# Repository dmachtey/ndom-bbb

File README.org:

* High density BBB domotic cape.
  - 32 opto inputs +32 opto outputs for BeagleBone Black
  - this board is intended to be used for domotics or whatever you
    want.
  - It has Push-in spring's connectors for easiness and space reduction
  - All inputs and outputs are gated though =GPIO3_15=
  - There are two more boards on this project:
    - "relay-board" is a single relay board.
    - "out-board" is a high current (10A) Mosfet Board intended for
      (soft) PWM LEDs, up to 60 volts

#+ATTR_LaTeX: :width 10cm\textwidth :options angle=0 :placement [H]
[[https://github.com/dmachtey/ndom-bbb/blob/master/images/domcape8.jpg]]

* Contact information
  - Damian Machtey
  - dmachtey at gmail com
* License
  - Hardware is released under [[http://creativecommons.org/licenses/by-sa/4.0/][Creative Commons Sharealike 4.0
    International]]
    [[file:https://i.creativecommons.org/l/by-sa/4.0/88x31.png]]
  - Software is released under GNU General Public License
    http://www.gnu.org/licenses/
  - © 2017 Damian Machtey

* Fell free to use this project
  - Just please let me know
  - and if you manufacture the board please keep my name on it.

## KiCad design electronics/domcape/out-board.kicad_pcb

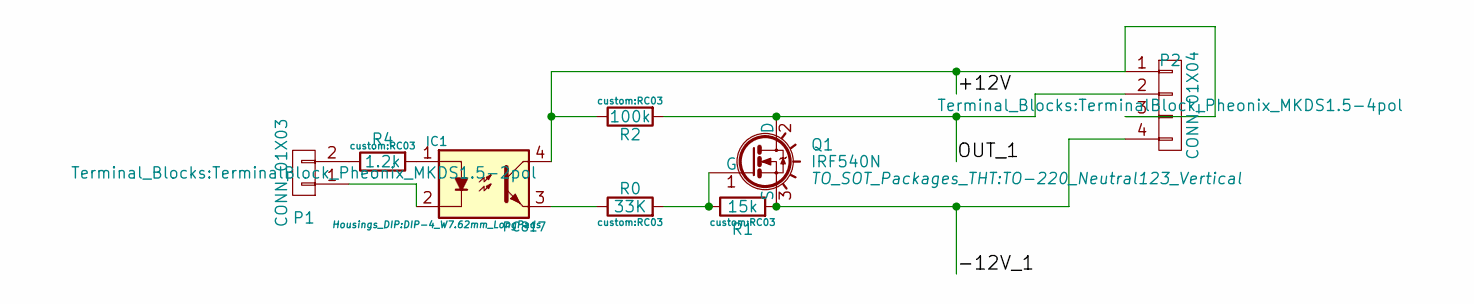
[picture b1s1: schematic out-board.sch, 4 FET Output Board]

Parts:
IC1: PC817; DIP-4_W7.62mm_LongPads
P1: CONN_01X03; TerminalBlock_Pheonix_MKDS1.5-2pol
P2: CONN_01X04; TerminalBlock_Pheonix_MKDS1.5-4pol
Q1: IRF540N; TO-220_Neutral123_Vertical
R0: 33K; RC03
R1: 15k; RC03
R2: 100k; RC03
R4: 1.2k; RC03

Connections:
/+12V: IC1.4, P2.1, P2.3, R2.1
/-12V_1: P2.4, Q1.3 (S), R1.2
/OUT_1: P2.2, Q1.2 (D), R2.2
unnamed: IC1.1, R4.2
unnamed: IC1.2, P1.1
unnamed: IC1.3, R0.1
unnamed: P1.2, R4.1
unnamed: Q1.1 (G), R0.2, R1.1

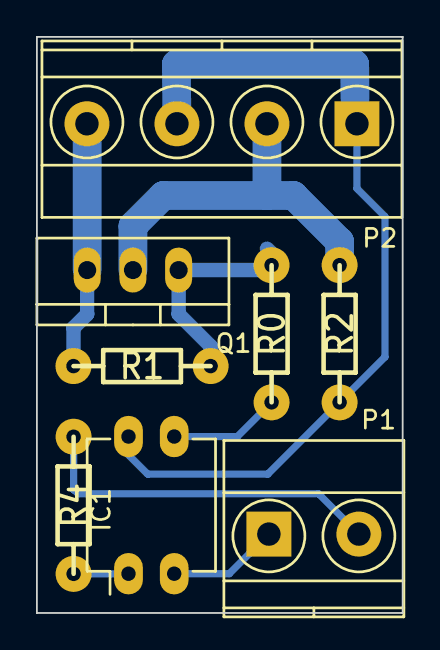
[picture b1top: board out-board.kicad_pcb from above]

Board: 2 copper layers, 20.3 x 32.0 mm, 8 parts (0 on the bottom side), 8 nets.

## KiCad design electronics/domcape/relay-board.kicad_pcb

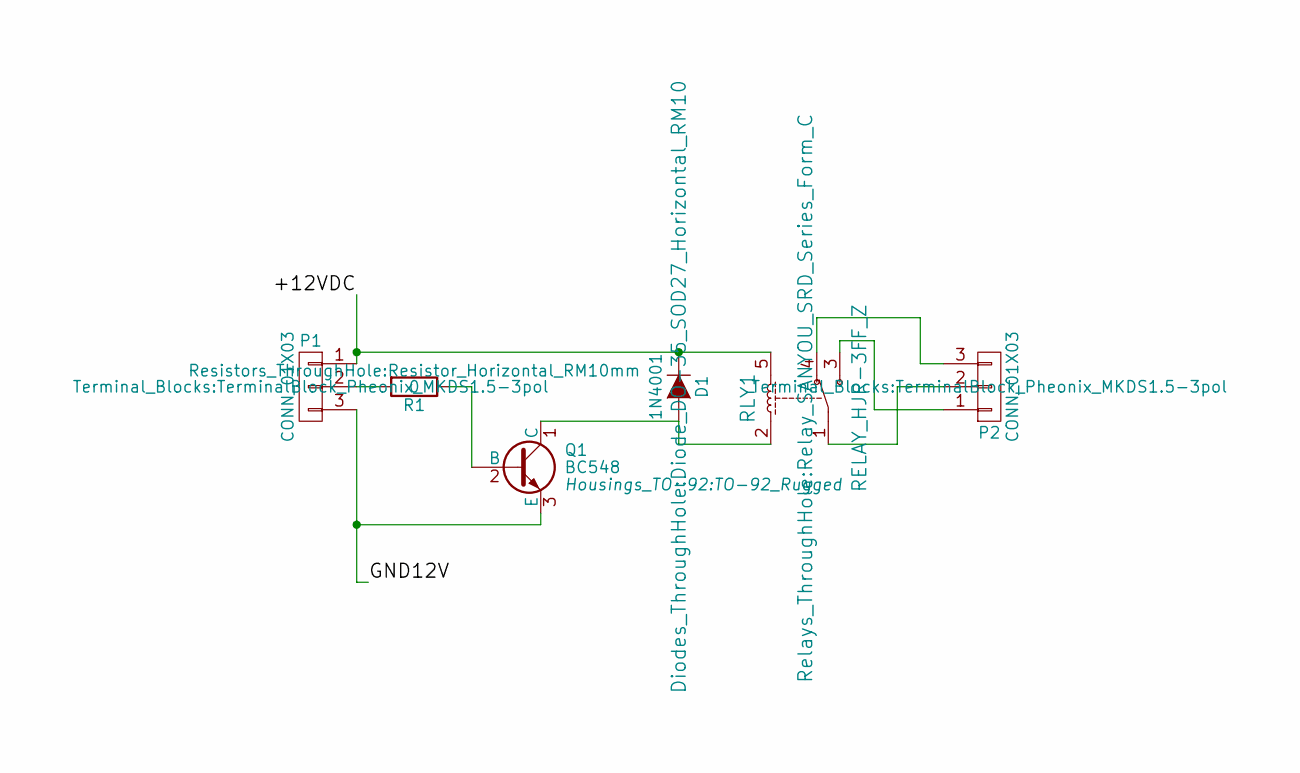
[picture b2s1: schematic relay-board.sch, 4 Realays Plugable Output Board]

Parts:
D1: 1N4001; Diode_DO-35_SOD27_Horizontal_RM10
P1, P2: CONN_01X03; TerminalBlock_Pheonix_MKDS1.5-3pol
Q1: BC548; TO-92_Rugged
R1: 0; Resistor_Horizontal_RM10mm
RLY1: RELAY_HJR-3FF_Z; Relay_SANYOU_SRD_Series_Form_C

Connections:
/+12VDC: D1.1 (K), P1.1, RLY1.5
/GND12V: P1.3, Q1.3 (E)
unnamed: D1.2 (A), Q1.1 (C), RLY1.2
unnamed: P1.2, R1.2
unnamed: P2.1, RLY1.3
unnamed: P2.2, RLY1.1
unnamed: P2.3, RLY1.4
unnamed: Q1.2 (B), R1.1

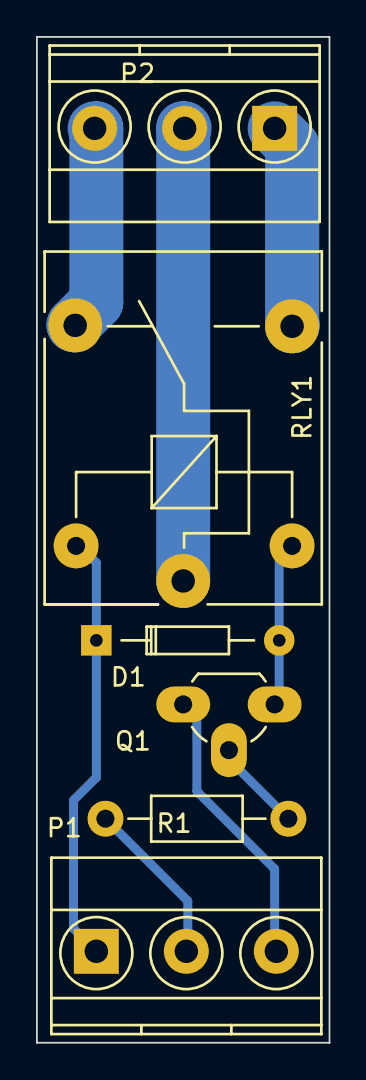
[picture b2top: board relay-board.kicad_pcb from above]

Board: 2 copper layers, 16.3 x 55.9 mm, 6 parts (0 on the bottom side), 8 nets.

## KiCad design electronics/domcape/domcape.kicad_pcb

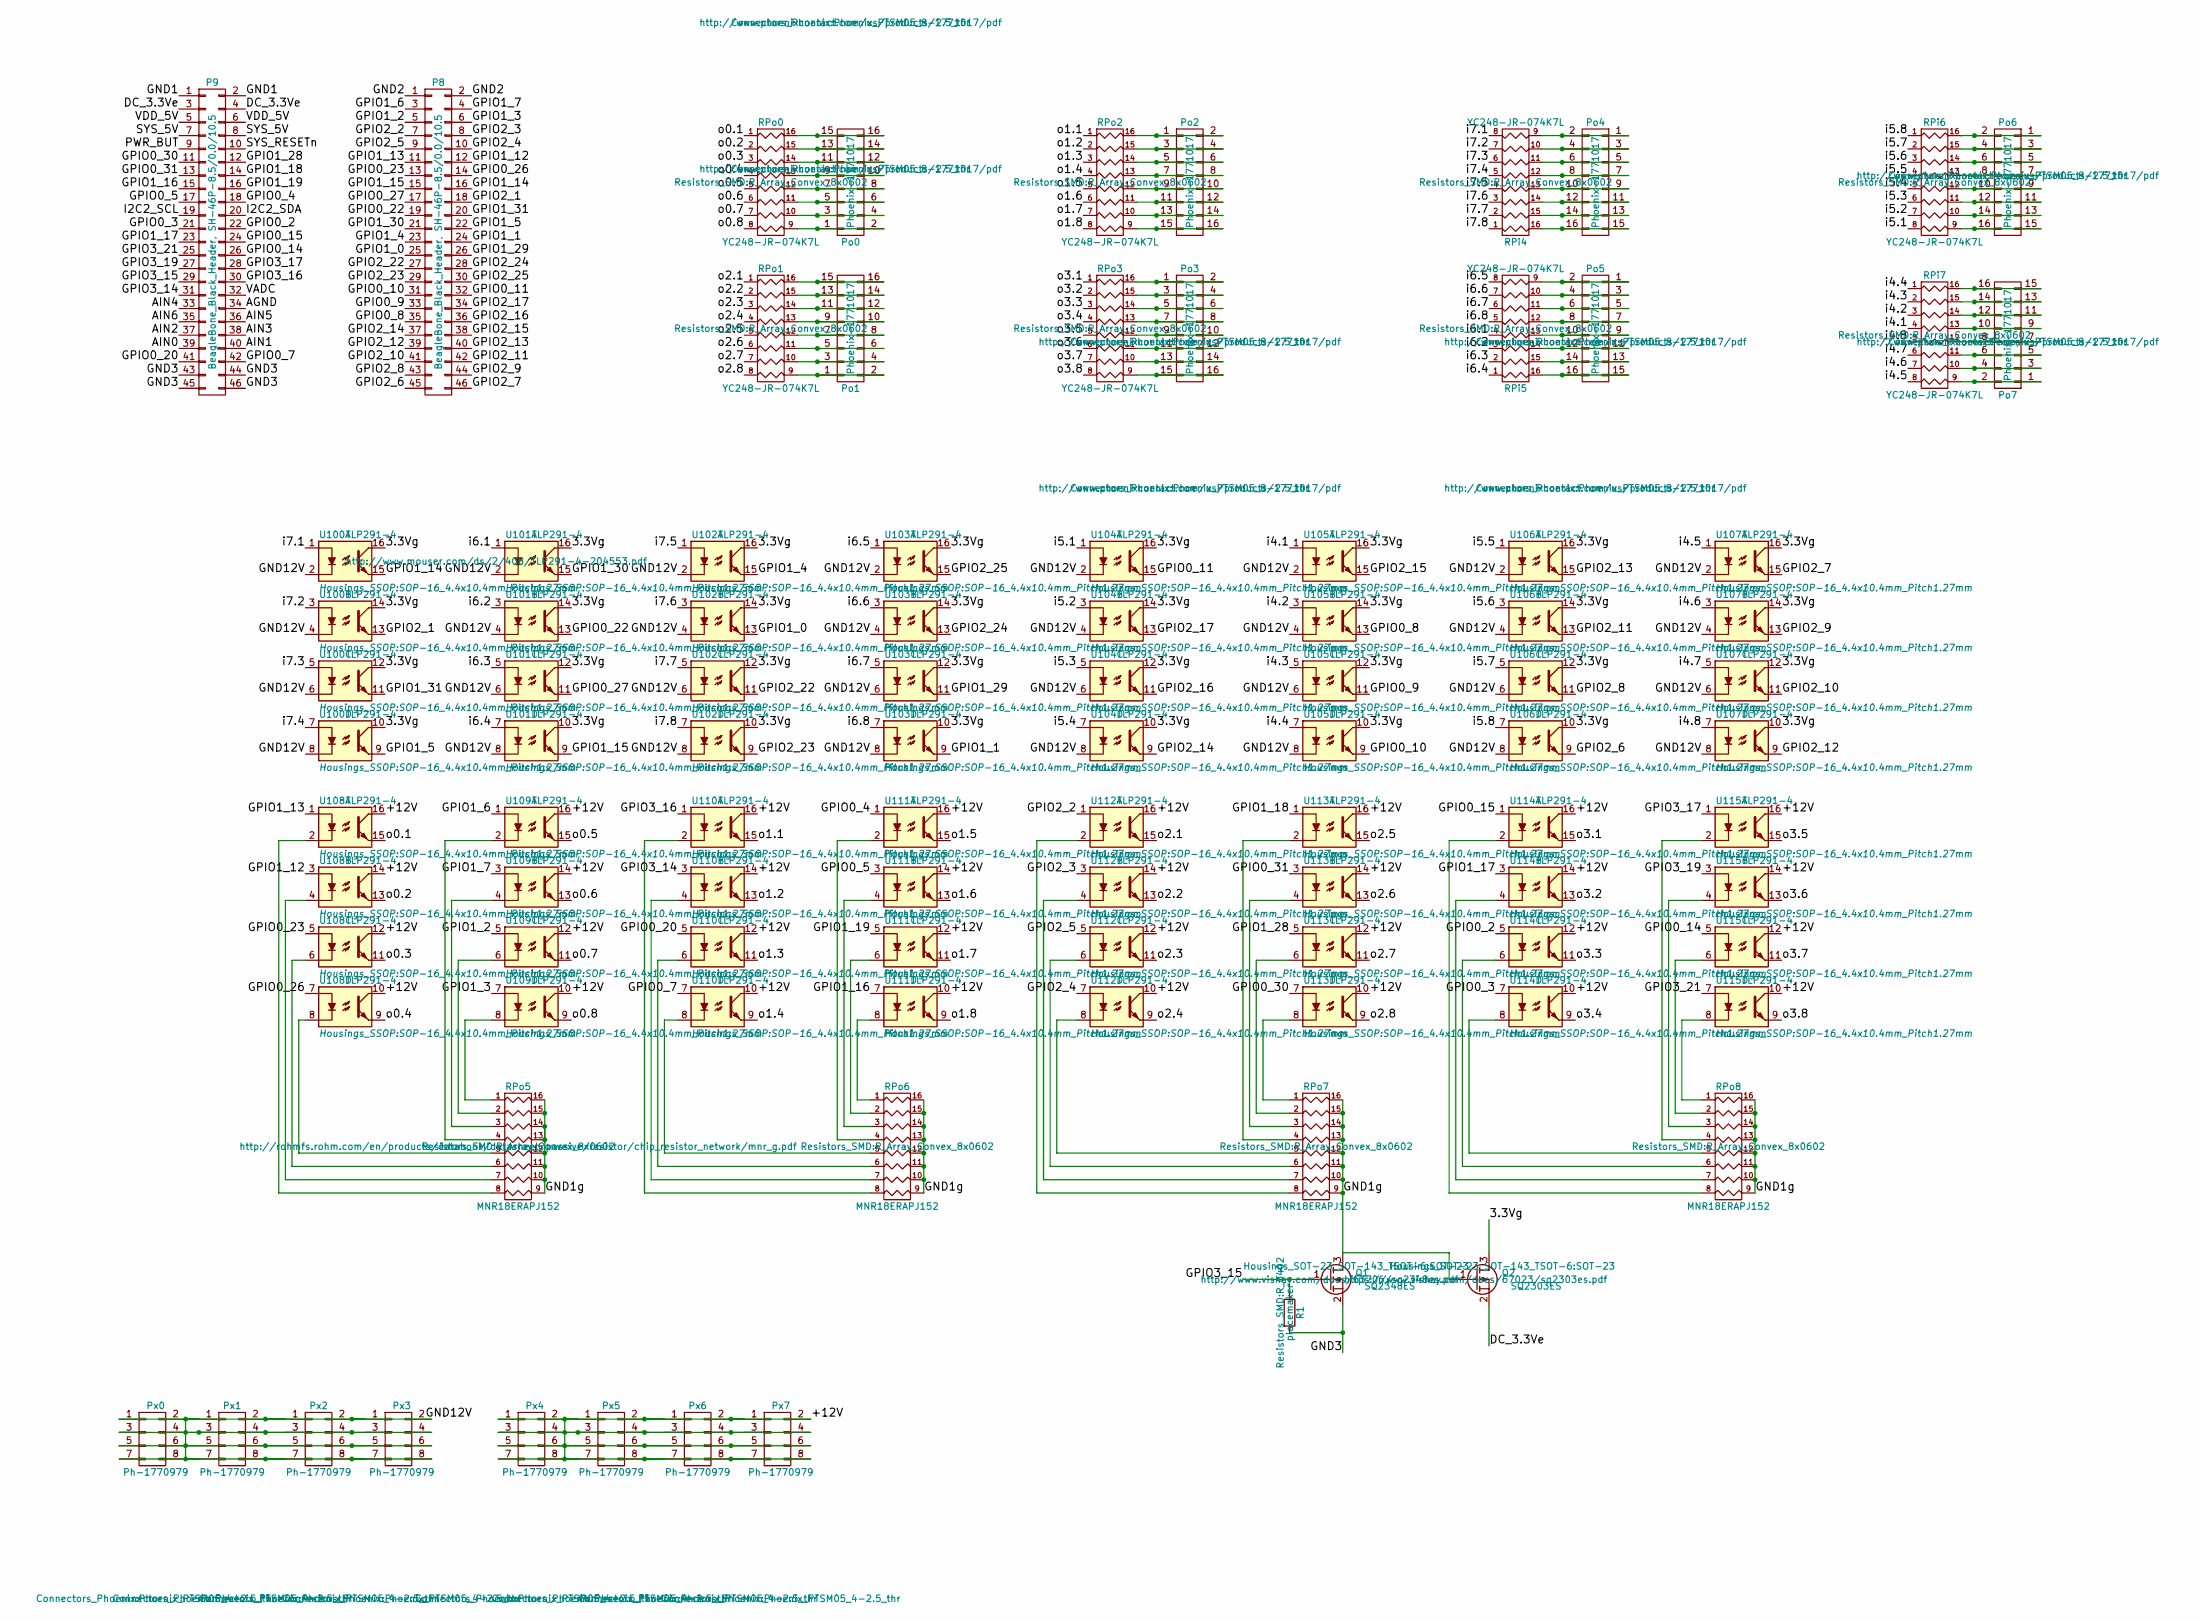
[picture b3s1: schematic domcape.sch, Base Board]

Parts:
P8, P9: BeagleBone_Black_Header, SH-46P-8.5/0.0/10.5
Po0, Po1, Po2, Po3, Po4, Po5, Po6, Po7: Phoenix-1771017; Phoenix_PTSM05_8-2.5_thr
Px0, Px1, Px2, Px3, Px4, Px5, Px6, Px7: Ph-1770979; Phoenix_PTSM05_4-2.5_thr
Q1: SQ2348ES; SOT-23
Q2: SQ2303ES; SOT-23
R1: placemaker; R_0402
RPi4, RPi5, RPi6, RPi7: YC248-JR-074K7L; R_Array_Convex_8x0602
RPo0, RPo1, RPo2, RPo3: YC248-JR-074K7L; R_Array_Convex_8x0602
RPo5, RPo6, RPo7, RPo8: MNR18ERAPJ152; R_Array_Convex_8x0602
U100, U101, U102, U103, U104, U105, U106, U107, U108, U109, U110, U111, U112, U113, U114, U115: TLP291-4; SOP-16_4.4x10.4mm_Pitch1.27mm

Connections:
/3.3Vg: Q2.3 (D), U100.10, U100.12, U100.14, U100.16, U101.10, U101.12, U101.14, U101.16, U102.10, U102.12, U102.14, U102.16, U103.10, U103.12, U103.14, U103.16, U104.10, U104.12, U104.14, U104.16, U105.10, U105.12, U105.14, U105.16, U106.10, U106.12, U106.14, U106.16, U107.10, U107.12, U107.14, U107.16
/+12V: Px4.1, Px4.2, Px4.3, Px4.4, Px4.5, Px4.6, Px4.7, Px4.8, Px5.1, Px5.2, Px5.3, Px5.4, Px5.5, Px5.6, Px5.7, Px5.8, Px6.1, Px6.2, Px6.3, Px6.4, Px6.5, Px6.6, Px6.7, Px6.8, Px7.1, Px7.2, Px7.3, Px7.4, Px7.5, Px7.6, Px7.7, Px7.8, U108.10, U108.12, U108.14, U108.16, U109.10, U109.12, U109.14, U109.16, U110.10, U110.12, U110.14, U110.16, U111.10, U111.12, U111.14, U111.16, U112.10, U112.12, U112.14, U112.16, U113.10, U113.12, U113.14, U113.16, U114.10, U114.12, U114.14, U114.16, U115.10, U115.12, U115.14, U115.16
/AGND: P9.34
/AIN0: P9.39
/AIN1: P9.40
/AIN2: P9.37
/AIN3: P9.38
/AIN4: P9.33
/AIN5: P9.36
/AIN6: P9.35
/DC_3.3Ve: P9.3, P9.4, Q2.2 (S)
/GND1: P9.1, P9.2
/GND1g: Q1.3 (D), Q2.1 (G), RPo5.9 (R8), RPo5.10 (R7), RPo5.11 (R6), RPo5.12 (R5), RPo5.13 (R4), RPo5.14 (R3), RPo5.15 (R2), RPo5.16 (R1), RPo6.9 (R8), RPo6.10 (R7), RPo6.11 (R6), RPo6.12 (R5), RPo6.13 (R4), RPo6.14 (R3), RPo6.15 (R2), RPo6.16 (R1), RPo7.9 (R8), RPo7.10 (R7), RPo7.11 (R6), RPo7.12 (R5), RPo7.13 (R4), RPo7.14 (R3), RPo7.15 (R2), RPo7.16 (R1), RPo8.9 (R8), RPo8.10 (R7), RPo8.11 (R6), RPo8.12 (R5), RPo8.13 (R4), RPo8.14 (R3), RPo8.15 (R2), RPo8.16 (R1)
/GND2: P8.1, P8.2
/GND3: P9.43, P9.44, P9.45, P9.46, Q1.2 (S), R1.2
/GND12V: Px0.1, Px0.2, Px0.3, Px0.4, Px0.5, Px0.6, Px0.7, Px0.8, Px1.1, Px1.2, Px1.3, Px1.4, Px1.5, Px1.6, Px1.7, Px1.8, Px2.1, Px2.2, Px2.3, Px2.4, Px2.5, Px2.6, Px2.7, Px2.8, Px3.1, Px3.2, Px3.3, Px3.4, Px3.5, Px3.6, Px3.7, Px3.8, U100.2, U100.4, U100.6, U100.8, U101.2, U101.4, U101.6, U101.8, U102.2, U102.4, U102.6, U102.8, U103.2, U103.4, U103.6, U103.8, U104.2, U104.4, U104.6, U104.8, U105.2, U105.4, U105.6, U105.8, U106.2, U106.4, U106.6, U106.8, U107.2, U107.4, U107.6, U107.8
/GPIO0_2: P9.22, U114.5
/GPIO0_3: P9.21, U114.7
/GPIO0_4: P9.18, U111.1
/GPIO0_5: P9.17, U111.3
/GPIO0_7: P9.42, U110.7
/GPIO0_8: P8.35, U105.13
/GPIO0_9: P8.33, U105.11
/GPIO0_10: P8.31, U105.9
/GPIO0_11: P8.32, U104.15
/GPIO0_14: P9.26, U115.5
/GPIO0_15: P9.24, U114.1
/GPIO0_20: P9.41, U110.5
/GPIO0_22: P8.19, U101.13
/GPIO0_23: P8.13, U108.5
/GPIO0_26: P8.14, U108.7
/GPIO0_27: P8.17, U101.11
/GPIO0_30: P9.11, U113.7
/GPIO0_31: P9.13, U113.3
/GPIO1_0: P8.25, U102.13
/GPIO1_1: P8.24, U103.9
/GPIO1_2: P8.5, U109.5
/GPIO1_3: P8.6, U109.7
/GPIO1_4: P8.23, U102.15
/GPIO1_5: P8.22, U100.9
/GPIO1_6: P8.3, U109.1
/GPIO1_7: P8.4, U109.3
/GPIO1_12: P8.12, U108.3
/GPIO1_13: P8.11, U108.1
/GPIO1_14: P8.16, U100.15
/GPIO1_15: P8.15, U101.9
/GPIO1_16: P9.15, U111.7
/GPIO1_17: P9.23, U114.3
/GPIO1_18: P9.14, U113.1
/GPIO1_19: P9.16, U111.5
/GPIO1_28: P9.12, U113.5
/GPIO1_29: P8.26, U103.11
/GPIO1_30: P8.21, U101.15
/GPIO1_31: P8.20, U100.11
/GPIO2_1: P8.18, U100.13
/GPIO2_2: P8.7, U112.1
/GPIO2_3: P8.8, U112.3
/GPIO2_4: P8.10, U112.7
/GPIO2_5: P8.9, U112.5
/GPIO2_6: P8.45, U106.9
/GPIO2_7: P8.46, U107.15
/GPIO2_8: P8.43, U106.11
/GPIO2_9: P8.44, U107.13
/GPIO2_10: P8.41, U107.11
/GPIO2_11: P8.42, U106.13
/GPIO2_12: P8.39, U107.9
/GPIO2_13: P8.40, U106.15
/GPIO2_14: P8.37, U104.9
/GPIO2_15: P8.38, U105.15
/GPIO2_16: P8.36, U104.11
/GPIO2_17: P8.34, U104.13
/GPIO2_22: P8.27, U102.11
/GPIO2_23: P8.29, U102.9
/GPIO2_24: P8.28, U103.13
/GPIO2_25: P8.30, U103.15
/GPIO3_14: P9.31, U110.3
/GPIO3_15: P9.29, Q1.1 (G), R1.1
/GPIO3_16: P9.30, U110.1
/GPIO3_17: P9.28, U115.1
/GPIO3_19: P9.27, U115.3
/GPIO3_21: P9.25, U115.7
/I2C2_SCL: P9.19
/I2C2_SDA: P9.20
/PWR_BUT: P9.9
/SYS_5V: P9.7, P9.8
/SYS_RESETn: P9.10
/VADC: P9.32
/VDD_5V: P9.5, P9.6
/i4.1: RPi7.4, U105.1
/i4.2: RPi7.3, U105.3
/i4.3: RPi7.2, U105.5
/i4.4: RPi7.1, U105.7
/i4.5: RPi7.8, U107.1
/i4.6: RPi7.7, U107.3
/i4.7: RPi7.6, U107.5
/i4.8: RPi7.5, U107.7
/i5.1: RPi6.8, U104.1
/i5.2: RPi6.7, U104.3
/i5.3: RPi6.6, U104.5
/i5.4: RPi6.5, U104.7
/i5.5: RPi6.4, U106.1
/i5.6: RPi6.3, U106.3
/i5.7: RPi6.2, U106.5
/i5.8: RPi6.1, U106.7
/i6.1: RPi5.4, U101.1
/i6.2: RPi5.3, U101.3
/i6.3: RPi5.2, U101.5
/i6.4: RPi5.1, U101.7
/i6.5: RPi5.8, U103.1
/i6.6: RPi5.7, U103.3
/i6.7: RPi5.6, U103.5
/i6.8: RPi5.5, U103.7
/i7.1: RPi4.8, U100.1
/i7.2: RPi4.7, U100.3
/i7.3: RPi4.6, U100.5
/i7.4: RPi4.5, U100.7
/i7.5: RPi4.4, U102.1
/i7.6: RPi4.3, U102.3
/i7.7: RPi4.2, U102.5
/i7.8: RPi4.1, U102.7
/o0.1: RPo0.1, U108.15
/o0.2: RPo0.2, U108.13
/o0.3: RPo0.3, U108.11
/o0.4: RPo0.4, U108.9
/o0.5: RPo0.5, U109.15
/o0.6: RPo0.6, U109.13
/o0.7: RPo0.7, U109.11
/o0.8: RPo0.8, U109.9
/o1.1: RPo2.1, U110.15
/o1.2: RPo2.2, U110.13
/o1.3: RPo2.3, U110.11
/o1.4: RPo2.4, U110.9
/o1.5: RPo2.5, U111.15
/o1.6: RPo2.6, U111.13
/o1.7: RPo2.7, U111.11
/o1.8: RPo2.8, U111.9
/o2.1: RPo1.1, U112.15
/o2.2: RPo1.2, U112.13
/o2.3: RPo1.3, U112.11
/o2.4: RPo1.4, U112.9
/o2.5: RPo1.5, U113.15
/o2.6: RPo1.6, U113.13
/o2.7: RPo1.7, U113.11
/o2.8: RPo1.8, U113.9
/o3.1: RPo3.1, U114.15
/o3.2: RPo3.2, U114.13
/o3.3: RPo3.3, U114.11
/o3.4: RPo3.4, U114.9
/o3.5: RPo3.5, U115.15
/o3.6: RPo3.6, U115.13
/o3.7: RPo3.7, U115.11
/o3.8: RPo3.8, U115.9
unnamed: Po0.1, Po0.2, RPo0.9 (R8)
unnamed: Po0.3, Po0.4, RPo0.10 (R7)
unnamed: Po0.5, Po0.6, RPo0.11 (R6)
unnamed: Po0.7, Po0.8, RPo0.12 (R5)
unnamed: Po0.9, Po0.10, RPo0.13 (R4)
unnamed: Po0.11, Po0.12, RPo0.14 (R3)
unnamed: Po0.13, Po0.14, RPo0.15 (R2)
unnamed: Po0.15, Po0.16, RPo0.16 (R1)
unnamed: Po1.1, Po1.2, RPo1.9 (R8)
unnamed: Po1.3, Po1.4, RPo1.10 (R7)
unnamed: Po1.5, Po1.6, RPo1.11 (R6)
unnamed: Po1.7, Po1.8, RPo1.12 (R5)
unnamed: Po1.9, Po1.10, RPo1.13 (R4)
unnamed: Po1.11, Po1.12, RPo1.14 (R3)
unnamed: Po1.13, Po1.14, RPo1.15 (R2)
unnamed: Po1.15, Po1.16, RPo1.16 (R1)
unnamed: Po2.1, Po2.2, RPo2.16 (R1)
unnamed: Po2.3, Po2.4, RPo2.15 (R2)
unnamed: Po2.5, Po2.6, RPo2.14 (R3)
unnamed: Po2.7, Po2.8, RPo2.13 (R4)
unnamed: Po2.9, Po2.10, RPo2.12 (R5)
unnamed: Po2.11, Po2.12, RPo2.11 (R6)
unnamed: Po2.13, Po2.14, RPo2.10 (R7)
unnamed: Po2.15, Po2.16, RPo2.9 (R8)
unnamed: Po3.1, Po3.2, RPo3.16 (R1)
unnamed: Po3.3, Po3.4, RPo3.15 (R2)
unnamed: Po3.5, Po3.6, RPo3.14 (R3)
unnamed: Po3.7, Po3.8, RPo3.13 (R4)
unnamed: Po3.9, Po3.10, RPo3.12 (R5)
unnamed: Po3.11, Po3.12, RPo3.11 (R6)
unnamed: Po3.13, Po3.14, RPo3.10 (R7)
unnamed: Po3.15, Po3.16, RPo3.9 (R8)
unnamed: Po4.1, Po4.2, RPi4.9 (R8)
unnamed: Po4.3, Po4.4, RPi4.10 (R7)
unnamed: Po4.5, Po4.6, RPi4.11 (R6)
unnamed: Po4.7, Po4.8, RPi4.12 (R5)
unnamed: Po4.9, Po4.10, RPi4.13 (R4)
unnamed: Po4.11, Po4.12, RPi4.14 (R3)
unnamed: Po4.13, Po4.14, RPi4.15 (R2)
unnamed: Po4.15, Po4.16, RPi4.16 (R1)
unnamed: Po5.1, Po5.2, RPi5.9 (R8)
unnamed: Po5.3, Po5.4, RPi5.10 (R7)
unnamed: Po5.5, Po5.6, RPi5.11 (R6)
unnamed: Po5.7, Po5.8, RPi5.12 (R5)
unnamed: Po5.9, Po5.10, RPi5.13 (R4)
unnamed: Po5.11, Po5.12, RPi5.14 (R3)
unnamed: Po5.13, Po5.14, RPi5.15 (R2)
unnamed: Po5.15, Po5.16, RPi5.16 (R1)
unnamed: Po6.1, Po6.2, RPi6.16 (R1)
unnamed: Po6.3, Po6.4, RPi6.15 (R2)
unnamed: Po6.5, Po6.6, RPi6.14 (R3)
unnamed: Po6.7, Po6.8, RPi6.13 (R4)
unnamed: Po6.9, Po6.10, RPi6.12 (R5)
unnamed: Po6.11, Po6.12, RPi6.11 (R6)
unnamed: Po6.13, Po6.14, RPi6.10 (R7)
unnamed: Po6.15, Po6.16, RPi6.9 (R8)
unnamed: Po7.1, Po7.2, RPi7.9 (R8)
unnamed: Po7.3, Po7.4, RPi7.10 (R7)
unnamed: Po7.5, Po7.6, RPi7.11 (R6)
unnamed: Po7.7, Po7.8, RPi7.12 (R5)
unnamed: Po7.9, Po7.10, RPi7.13 (R4)
unnamed: Po7.11, Po7.12, RPi7.14 (R3)
unnamed: Po7.13, Po7.14, RPi7.15 (R2)
unnamed: Po7.15, Po7.16, RPi7.16 (R1)
unnamed: RPo5.1, U109.8
unnamed: RPo5.2, U109.6
unnamed: RPo5.3, U109.4
unnamed: RPo5.4, U109.2
unnamed: RPo5.5, U108.8
unnamed: RPo5.6, U108.6
unnamed: RPo5.7, U108.4
unnamed: RPo5.8, U108.2
unnamed: RPo6.1, U111.8
unnamed: RPo6.2, U111.6
unnamed: RPo6.3, U111.4
unnamed: RPo6.4, U111.2
unnamed: RPo6.5, U110.8
unnamed: RPo6.6, U110.6
unnamed: RPo6.7, U110.4
unnamed: RPo6.8, U110.2
unnamed: RPo7.1, U113.8
unnamed: RPo7.2, U113.6
unnamed: RPo7.3, U113.4
unnamed: RPo7.4, U113.2
unnamed: RPo7.5, U112.8
unnamed: RPo7.6, U112.6
unnamed: RPo7.7, U112.4
unnamed: RPo7.8, U112.2
unnamed: RPo8.1, U115.8
unnamed: RPo8.2, U115.6
unnamed: RPo8.3, U115.4
unnamed: RPo8.4, U115.2
unnamed: RPo8.5, U114.8
unnamed: RPo8.6, U114.6
unnamed: RPo8.7, U114.4
unnamed: RPo8.8, U114.2

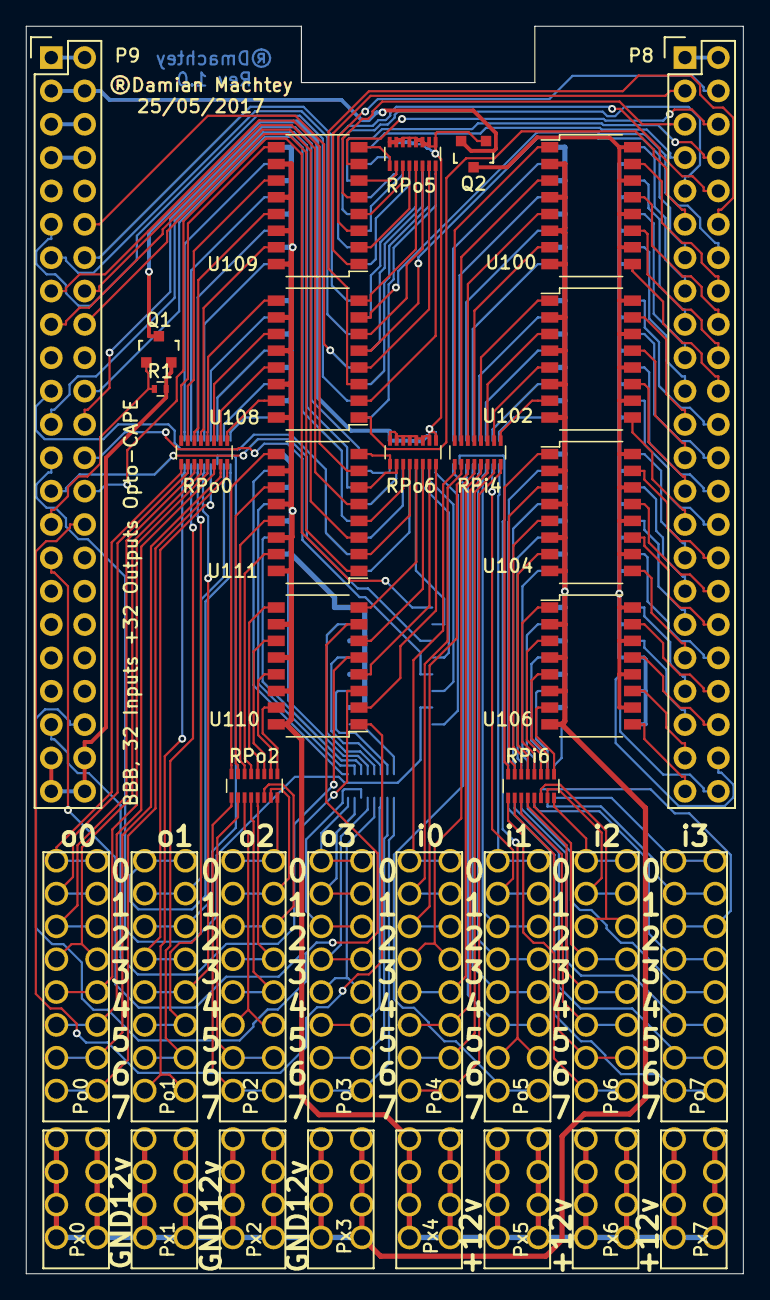
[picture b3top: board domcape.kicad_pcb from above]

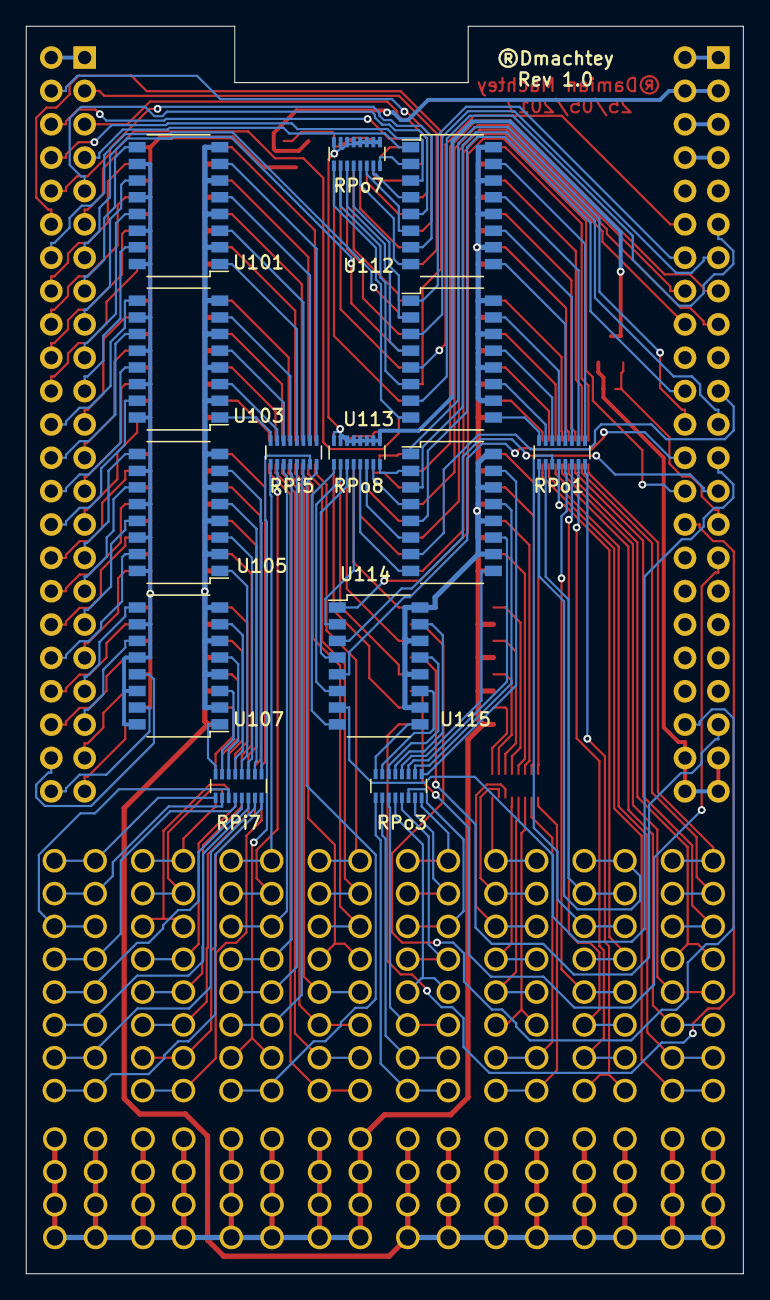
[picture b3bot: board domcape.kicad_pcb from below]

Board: 2 copper layers, 54.6 x 95.0 mm, 49 parts (14 on the bottom side), 235 nets.

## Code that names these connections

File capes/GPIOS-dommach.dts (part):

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     		    /* INPUT   GPIO(mode7) 0x27 pulldown, 0x37 pullup, 0x?f no pullup/down */
                //Address  Mode   | BBB Port | gpio number | Slot | Order | Mode 7   | Mode  | Mode | Comment |   |   |
                //----------------+----------+-------------+------+-------+----------+-------+------+---------+---+---|
                0x194  0x07  // | P9_29    |         111 | -    |     - | GPIO3_15 | SPI     |      | BoardEn |         |   |   |
                0x038  0x07  // | P8_16    |          46 | i4   |     0 | GPIO1_14 |         |      |         |         |   |   |
                0x08c  0x07  // | P8_18    |          65 | i4   |     1 | GPIO2_1  |         |      |         |         |   |   |
                0x084  0x07  // | P8_20    |          63 | i4   |     2 | GPIO1_31 | UART4   |      |         |         |   |   |
                0x014  0x07  // | P8_22    |          37 | i4   |     3 | GPIO1_5  |         |      |         |         |   |   |
                0x010  0x07  // | P8_23    |          36 | i4   |     4 | GPIO1_4  |         |      |         |         |   |   |
                0x000  0x07  // | P8_25    |          32 | i4   |     5 | GPIO1_0  |         |      |         |         |   |   |
                0x0E0  0x07  // | P8_27    |          86 | i4   |     6 | GPIO2_22 |         |      |         |         |   |   |
                0x0E4  0x07  // | P8_29    |          87 | i4   |     7 | GPIO2_23 |         |      |         |         |   |   |
                0x0EC  0x07  // | P8_30    |          89 | i5   |     0 | GPIO2_25 |         |      |         |         |   |   |
                0x0E8  0x07  // | P8_28    |          88 | i5   |     1 | GPIO2_24 |         |      |         |         |   |   |
                0x07c  0x07  // | P8_26    |          61 | i5   |     2 | GPIO1_29 |         |      |         |         |   |   |
                0x004  0x07  // | P8_24    |          33 | i5   |     3 | GPIO1_1  |         |      |         |         |   |   |
                0x080  0x07  // | P8_21    |          62 | i5   |     4 | GPIO1_30 | UART4   |      |         |         |   |   |
                0x020  0x07  // | P8_19    |          22 | i5   |     5 | GPIO0_22 |         |      |         |         |   |   |
                0x02c  0x07  // | P8_17    |          27 | i5   |     6 | GPIO0_27 |         |      |         |         |   |   |
                0x03c  0x07  // | P8_15    |          47 | i5   |     7 | GPIO1_15 |         |      |         |         |   |   |
                0x0A0  0x07  // | P8_45    |          70 | i6   |     0 | GPIO2_6  |         |      |         |         |   |   |
                0x0A8  0x07  // | P8_43    |          72 | i6   |     1 | GPIO2_8  |         |      |         |         |   |   |
                0x0B4  0x07  // | P8_42    |          75 | i6   |     2 | GPIO2_11 |         |      |         |         |   |   |
                0x0BC  0x07  // | P8_40    |          77 | i6   |     3 | GPIO2_13 |         |      |         |         |   |   |
                0x0C0  0x07  // | P8_37    |          78 | i6   |     4 | GPIO2_14 |         |      |         |         |   |   |
                0x0C8  0x07  // | P8_36    |          80 | i6   |     5 | GPIO2_16 |         |      |         |         |   |   |
                0x0CC  0x07  // | P8_34    |          81 | i6   |     6 | GPIO2_17 |         |      |         |         |   |   |
                0x0DC  0x07  // | P8_32    |          11 | i6   |     7 | GPIO0_11 |         |      |         |         |   |   |
                0x0A4  0x07  // | P8_46    |          71 | i7   |     0 | GPIO2_7  |         |      |         |         |   |   |
                0x0AC  0x07  // | P8_44    |          73 | i7   |     1 | GPIO2_9  |         |      |         |         |   |   |
                0x0B0  0x07  // | P8_41    |          74 | i7   |     2 | GPIO2_10 |         |      |         |         |   |   |
                0x0B8  0x07  // | P8_39    |          76 | i7   |     3 | GPIO2_12 |         |      |         |         |   |   |
                0x0C4  0x07  // | P8_38    |          79 | i7   |     4 | GPIO2_15 |         |      |         |         |   |   |
                0x0D0  0x07  // | P8_35    |           8 | i7   |     5 | GPIO0_8  |         |      |         |         |   |   |
                0x0D4  0x07  // | P8_33    |           9 | i7   |     6 | GPIO0_9  |         |      |         |         |   |   |
                0x0D8  0x07  // | P8_31    |          10 | i7   |     7 | GPIO0_10 |         |      |         |         |   |   |

                0x00c  0x07  // | P8_06    |          35 | o0   |     0 | GPIO1_3  |         |      |         |         |   |   |
                0x008  0x07  // | P8_05    |          34 | o0   |     1 | GPIO1_2  |         |      |         |         |   |   |
                0x01c  0x07  // | P8_04    |          39 | o0   |     2 | GPIO1_7  |         |      |         |         |   |   |
                0x018  0x07  // | P8_03    |          38 | o0   |     3 | GPIO1_6  |         |      | ??      |         |   |   |
                0x028  0x07  // | P8_14    |          26 | o0   |     4 | GPIO0_26 |         |      |         |         |   |   |
                0x024  0x07  // | P8_13    |          23 | o0   |     5 | GPIO0_23 |         |      |         |         |   |   |
                0x030  0x07  // | P8_12    |          44 | o0   |     6 | GPIO1_12 |         |      |         |         |   |   |
                0x034  0x07  // | P8_11    |          45 | o0   |     7 | GPIO1_13 |         |      |         |         |   |   |
                0x070  0x07  // | P9_11    |          30 | o1   |     0 | GPIO0_30 |         |      |         |         |   |   |
                0x078  0x07  // | P9_12    |          60 | o1   |     1 | GPIO1_28 |         |      |         |         |   |   |
                0x074  0x07  // | P9_13    |          31 | o1   |     2 | GPIO0_31 |         |      |         |         |   |   |
                0x048  0x07  // | P9_14    |          50 | o1   |     3 | GPIO1_18 |         |      |         |         |   |   |
                0x098  0x07  // | P8_10    |          68 | o1   |     4 | GPIO2_4  |         |      |         |         |   |   |
                0x09c  0x07  // | P8_09    |          69 | o1   |     5 | GPIO2_5  |         |      |         |         |   |   |
                0x094  0x07  // | P8_08    |          67 | o1   |     6 | GPIO2_3  |         |      |         |         |   |   |
                0x090  0x07  // | P8_07    |          66 | o1   |     7 | GPIO2_2  |         |      |         |         |   |   |
                0x198  0x07  // | P9_30    |         112 | o2   |     0 | GPIO3_16 | SPI     |      |         |         |   |   |
                0x190  0x07  // | P9_31    |         110 | o2   |     1 | GPIO3_14 | SPI     |      |         |         |   |   |
                0x1b4  0x07  // | P9_41    |          20 | o2   |     2 | GPIO0_20 |         |      |         |         |   |   |
                0x164  0x07  // | P9_42    |           7 | o2   |     3 | GPIO0_7  |         |      |         |         |   |   |
                0x158  0x07  // | P9_18    |           4 | o2   |     4 | GPIO0_4  | I2C1    |      |         |         |   |   |
                0x15c  0x07  // | P9_17    |           5 | o2   |     5 | GPIO0_5  | I2C1    |      |         |         |   |   |
                0x04c  0x07  // | P9_16    |          51 | o2   |     6 | GPIO1_19 |         |      |         |         |   |   |
                0x040  0x07  // | P9_15    |          48 | o2   |     7 | GPIO1_16 |         |      |         |         |   |   |
                0x184  0x07  // | P9_24    |          15 | o3   |     0 | GPIO0_15 | UART1   | I2C1 |         |         |   |   |
                0x044  0x07  // | P9_23    |          49 | o3   |     1 | GPIO1_17 |         |      |         |         |   |   |
                0x150  0x07  // | P9_22    |           2 | o3   |     2 | GPIO0_2  | UART2   | I2C2 |         |         |   |   |
                0x154  0x07  // | P9_21    |           3 | o3   |     3 | GPIO0_3  | UART2   | I2C2 |         |         |   |   |
                0x19c  0x07  // | P9_28    |         113 | o3   |     4 | GPIO3_17 | SPI     |      |         |         |   |   |
                0x1a4  0x07  // | P9_27    |         115 | o3   |     5 | GPIO3_19 |         |      |         |         |   |   |
                0x180  0x07  // | P9_26    |          14 | o3   |     6 | GPIO0_14 | UART1   | I2C1 |         |         |   |   |
                0x1ac  0x07  // | P9_25    |         117 | o3   |     7 | GPIO3_21 |         |      |         |         |   |   |
                >;
            };
            pru_pru_pins: pinmux_pru_pru_pins {   // The PRU pin modes
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
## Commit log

2017-06-12 readme
2017-06-12 new images
2017-07-06 Ploting mods
2017-08-03 add notes, and minor changes
2017-08-30 notes update
2017-08-30 File renamed
2017-09-10 testing, src & case
2017-09-10 code aesthetic
2017-09-10 License notice update
2017-09-10 minor typos
2017-09-10 new photos
2017-09-10 problems
2017-09-15 out-board circuit corrections

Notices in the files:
capes/GPIOS-dommach.dts:
Copyright 2013
This program is free software; you can redistribute it and/or modify
it under the terms of the GNU General Public License as published by
the Free Software Foundation; either version 2 of the License, or
(at your option) any later version.
